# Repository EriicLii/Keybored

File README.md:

# Keybored65
Project moved to https://github.com/N0S-Party/Staccato65

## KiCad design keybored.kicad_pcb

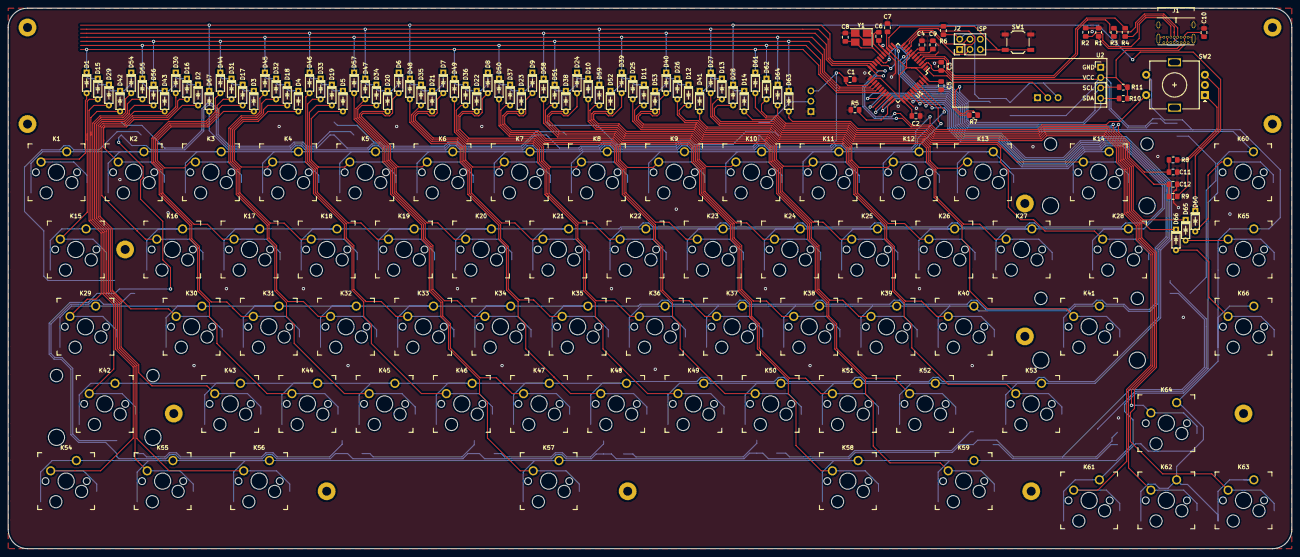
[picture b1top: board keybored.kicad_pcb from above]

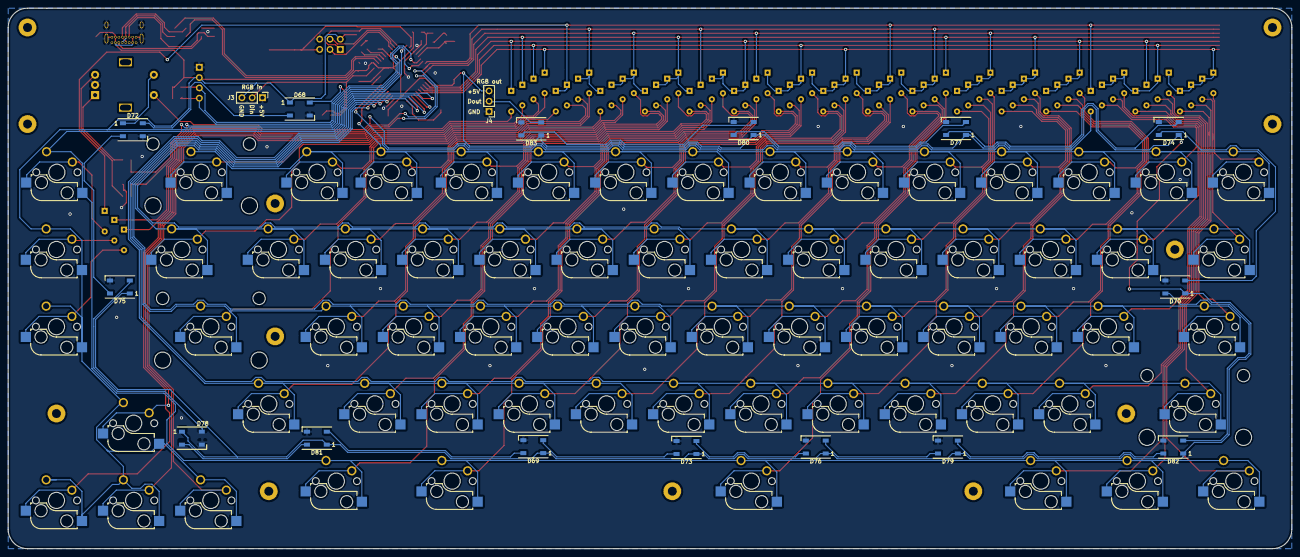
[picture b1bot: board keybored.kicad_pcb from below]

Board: 2 copper layers, 316.7 x 133.3 mm, 180 parts (17 on the bottom side), 123 nets.

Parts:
C1, C2, C3, C4, C5, C7: 0.1u; C_0805_2012Metric_Pad1.15x1.40mm_HandSolder
C6, C8: 22p; C_0805_2012Metric_Pad1.15x1.40mm_HandSolder
C9: 1u; C_0805_2012Metric_Pad1.15x1.40mm_HandSolder
C10: 4.7u; C_0805_2012Metric_Pad1.15x1.40mm_HandSolder
C11, C12: 100n; C_0805_2012Metric_Pad1.15x1.40mm_HandSolder
D1, D2, D3, D4, D5, D6, D7, D8, D9, D10, D11, D12, D13, D14, D15, D16, D17, D18, D19, D20, D21, D22, D23, D24, D25, D26, D27, D28, D29, D30, D31, D32, D33, D34, D35, D36, D37, D38, D39, D40, D41, D42, D43, D44, D45, D46, D47, D48, D49, D50, D51, D52, D53, D54, D55, D56, D57, D58, D59, D60, D61, D62, D63, D64, D65, D66, D67: D; DO-35_SOD27_5.08mm
D68, D69, D70, D72, D73, D74, D75, D76, D77, D78, D79, D80, D81, D82, D83: WS2812B; LED_WS2812B_PLCC4_5.0x5.0mm_P3.2mm
J1: USB_C_Receptacle_USB2.0; USB_C_GCT_USB4085
J2: ISP; PinHeader_2x03_P2.54mm_Vertical
J3: RGB in; PinHeader_1x03_P2.54mm_Vertical
J4: RGB out; PinHeader_1x03_P2.54mm_Vertical
K1, K2, K3, K4, K5, K6, K7, K8, K9, K10, K11, K12, K13, K14, K15, K16, K17, K18, K19, K20, K21, K22, K23, K24, K25, K26, K27, K28, K29, K30, K31, K32, K33, K34, K35, K36, K37, K38, K39, K40, K41, K42, K43, K44, K45, K46, K47, K48, K49, K50, K51, K52, K53, K54, K55, K56, K57, K58, K59, K60, K61, K62, K63, K64, K65, K66: KEYSW; Kailh_socket_MX_optional
R1, R2: 5.1k; R_0805_2012Metric_Pad1.15x1.40mm_HandSolder
R3, R4: 22; R_0805_2012Metric_Pad1.15x1.40mm_HandSolder
R5, R6: 10k; R_0805_2012Metric_Pad1.15x1.40mm_HandSolder
R7: 330; R_0805_2012Metric_Pad1.15x1.40mm_HandSolder
R8, R9: 27k; R_0805_2012Metric_Pad1.15x1.40mm_HandSolder
R10, R11: 4.7k; R_0805_2012Metric_Pad1.15x1.40mm_HandSolder
SW1: SW_PUSH; SW_SPST_TL3342
SW2: Rot_Enc_Sw; RotaryEncoder_Alps_EC11E-Switch_Vertical_H20mm
U1: ATMEGA32U4; TQFP-44_10x10mm_P0.8mm
U2: SSD1306-Display_Graphic; SSD1306_OLED_128x32_0.91_inch
Y1: Crystal; Crystal_SMD_SeikoEpson_FA238-4Pin_3.2x2.5mm_HandSoldering

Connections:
GND: C1.2, C2.2, C3.2, C4.2, C5.2, C6.2, C7.2, C8.2, C9.2, C10.2, C11.2, C12.1, D68.3, D69.3, D70.3, D72.3, D73.3, D74.3, D75.3, D76.3, D77.3, D78.3, D79.3, D80.3, D81.3, D82.3, D83.3, J1.A1, J1.A12, J1.B1, J1.B12, J1.S1, J2.6, J3.1, J4.1, R1.1, R2.1, R5.1, SW1.1, SW2.C, U1.5, U1.15, U1.23, U1.35, U1.43, U2.1, Y1.2, Y1.4
I2C_SCL: R11.1, U1.18, U2.3
I2C_SDA: R10.1, U1.19, U2.4
MISO: J2.1, U1.11
MOSI: J2.4, U1.10
unnamed: C6.1, U1.16, Y1.1
unnamed: C8.1, U1.17, Y1.3
unnamed: C9.1, U1.6
unnamed: D1.2, K1.2
unnamed: D2.2, K2.2
unnamed: D3.2, K3.2
unnamed: D4.2, K4.2
unnamed: D5.2, K5.2
unnamed: D6.2, K6.2
unnamed: D7.2, K7.2
unnamed: D8.2, K8.2
unnamed: D9.2, K9.2
unnamed: D10.2, K10.2
unnamed: D11.2, K11.2
unnamed: D12.2, K12.2
unnamed: D13.2, K13.2
unnamed: D14.2, K14.2
unnamed: D15.2, K15.2
unnamed: D16.2, K16.2
unnamed: D17.2, K17.2
unnamed: D18.2, K18.2
unnamed: D19.2, K19.2
unnamed: D20.2, K20.2
unnamed: D21.2, K21.2
unnamed: D22.2, K22.2
unnamed: D23.2, K23.2
unnamed: D24.2, K24.2
unnamed: D25.2, K25.2
unnamed: D26.2, K26.2
unnamed: D27.2, K27.2
unnamed: D28.2, K28.2
unnamed: D29.2, K29.2
unnamed: D30.2, K30.2
unnamed: D31.2, K31.2
unnamed: D32.2, K32.2
unnamed: D33.2, K33.2
unnamed: D34.2, K34.2
unnamed: D35.2, K35.2
unnamed: D36.2, K36.2
unnamed: D37.2, K37.2
unnamed: D38.2, K38.2
unnamed: D39.2, K39.2
unnamed: D40.2, K40.2
unnamed: D41.2, K41.2
unnamed: D42.2, K42.2
unnamed: D43.2, K43.2
unnamed: D44.2, K44.2
unnamed: D45.2, K45.2
unnamed: D46.2, K46.2
unnamed: D47.2, K47.2
unnamed: D48.2, K48.2
unnamed: D49.2, K49.2
unnamed: D50.2, K50.2
unnamed: D51.2, K51.2
unnamed: D52.2, K52.2
unnamed: D53.2, K53.2
unnamed: D54.2, K54.2
unnamed: D55.2, K55.2
unnamed: D56.2, K56.2
unnamed: D57.2, K57.2
unnamed: D58.2, K58.2
unnamed: D59.2, K59.2
unnamed: D60.2, K60.2
unnamed: D61.2, K61.2
unnamed: D62.2, K62.2
unnamed: D63.2, K63.2
unnamed: D64.2, K64.2
unnamed: D65.2, K65.2
unnamed: D66.2, K66.2
unnamed: D68.2, D72.4
unnamed: D68.4, R7.1
unnamed: D69.2, D73.4
unnamed: D69.4, D81.2
unnamed: D70.2, D74.4
unnamed: D70.4, D82.2
unnamed: D72.2, D75.4
unnamed: D73.2, D76.4
unnamed: D74.2, D77.4
unnamed: D75.2, D78.4
unnamed: D76.2, D79.4
unnamed: D77.2, D80.4
unnamed: D78.2, D81.4
unnamed: D79.2, D82.4
unnamed: D80.2, D83.4
unnamed: J1.A5, R1.2
unnamed: J1.B5, R2.2
unnamed: R3.1, U1.3
unnamed: R4.1, U1.4
unnamed: R5.2, U1.33
unnamed: R8.1, SW2.A
unnamed: R9.2, SW2.B
RESET: J2.5, R6.2, SW1.2, U1.13
RGB_IN: J3.2, R7.2, U1.1
RGB_OUT: D83.2, J4.2
SCK: J2.3, U1.9
USB_D+: J1.A6, J1.B6, R4.2
USB_D-: J1.A7, J1.B7, R3.2
VCC: C1.1, C2.1, C3.1, C4.1, C5.1, C7.1, C10.1, D68.1, D69.1, D70.1, D72.1, D73.1, D74.1, D75.1, D76.1, D77.1, D78.1, D79.1, D80.1, D81.1, D82.1, D83.1, J1.A4, J1.A9, J1.B4, J1.B9, J2.2, J3.3, J4.3, R6.1, R10.2, R11.2, U1.2, U1.7, U1.14, U1.24, U1.34, U1.44, U2.2
col0: K1.1, K2.1, K3.1, K4.1, K5.1, K6.1, K7.1, U1.41
col1: K8.1, K9.1, K10.1, K11.1, K12.1, K13.1, K14.1, U1.40
col2: K15.1, K16.1, K17.1, K18.1, K19.1, K20.1, K21.1, U1.39
col3: K22.1, K23.1, K24.1, K25.1, K26.1, K27.1, K28.1, U1.38
col4: K29.1, K30.1, K31.1, K32.1, K33.1, K34.1, K35.1, U1.37
col5: K36.1, K37.1, K38.1, K39.1, K40.1, K41.1, U1.36
col6: K42.1, K43.1, K44.1, K45.1, K46.1, K47.1, K48.1, U1.32
col7: K49.1, K50.1, K51.1, K52.1, K53.1, U1.31
col8: K54.1, K55.1, K56.1, K57.1, K58.1, K59.1, K60.1, U1.30
col9: K61.1, K62.1, K63.1, K64.1, K65.1, K66.1, SW2.S1, U1.29
rotA: C11.1, R8.2, U1.12
rotB: C12.2, R9.1, U1.8
rotSw2: D67.2, SW2.S2
row0: D1.1, D8.1, D15.1, D22.1, D29.1, D36.1, D42.1, D49.1, D54.1, D61.1, U1.28
row1: D2.1, D9.1, D16.1, D23.1, D30.1, D37.1, D43.1, D50.1, D55.1, D62.1, U1.27
row2: D3.1, D10.1, D17.1, D24.1, D31.1, D38.1, D44.1, D51.1, D56.1, D63.1, U1.26
row3: D4.1, D11.1, D18.1, D25.1, D32.1, D39.1, D45.1, D52.1, D57.1, D64.1, U1.25
row4: D5.1, D12.1, D19.1, D26.1, D33.1, D40.1, D46.1, D53.1, D58.1, D65.1, U1.22
row5: D6.1, D13.1, D20.1, D27.1, D34.1, D41.1, D47.1, D59.1, D66.1, U1.21
row6: D7.1, D14.1, D21.1, D28.1, D35.1, D48.1, D60.1, D67.1, U1.20

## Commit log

2020-08-14 Fix typo in README
2020-08-18 Major pcb changes
    - now uses a dual footprint for switches
    - added ARGB support
    - added stabilizer holes
    - added header pin support for ISP
